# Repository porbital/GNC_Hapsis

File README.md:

# GNC_Hapsis

Software and hardware for GNC Hapsis.

    If you have any questions, please reach out to Matthew Allen on Slack.

## STAG Software 

The C++ code is stored in `STAG/flight_controller_v3`.

This was developed using PlatformIO, but can be used with Arduino IDE as well.

The current software is complete and will be used on the STAG mission. 

Hardware-in-the-loop is possible with this code setup, and can be enabled by commenting out the flag in `config.h`

## STAG PCB

The PCB for this project (version 4.1) is stored under `polaris4.1/`.

The current PCB is fully complete. I assembled it without a stencil, using solder paste and a hot plate. (In the future, it is worth buying a stencil).

### AI Transparency Statement

As I'm sure you all are aware, AI is an incredibly powerful tool. However, I think that it is important to be honest and clear regarding how it is utilized in a project, especially one of this nature.

AI was used for debugging, research, and some code generation (primarily autocomplete and boilerplate code). It also generated the flight visualization script.

# Go Orbital!

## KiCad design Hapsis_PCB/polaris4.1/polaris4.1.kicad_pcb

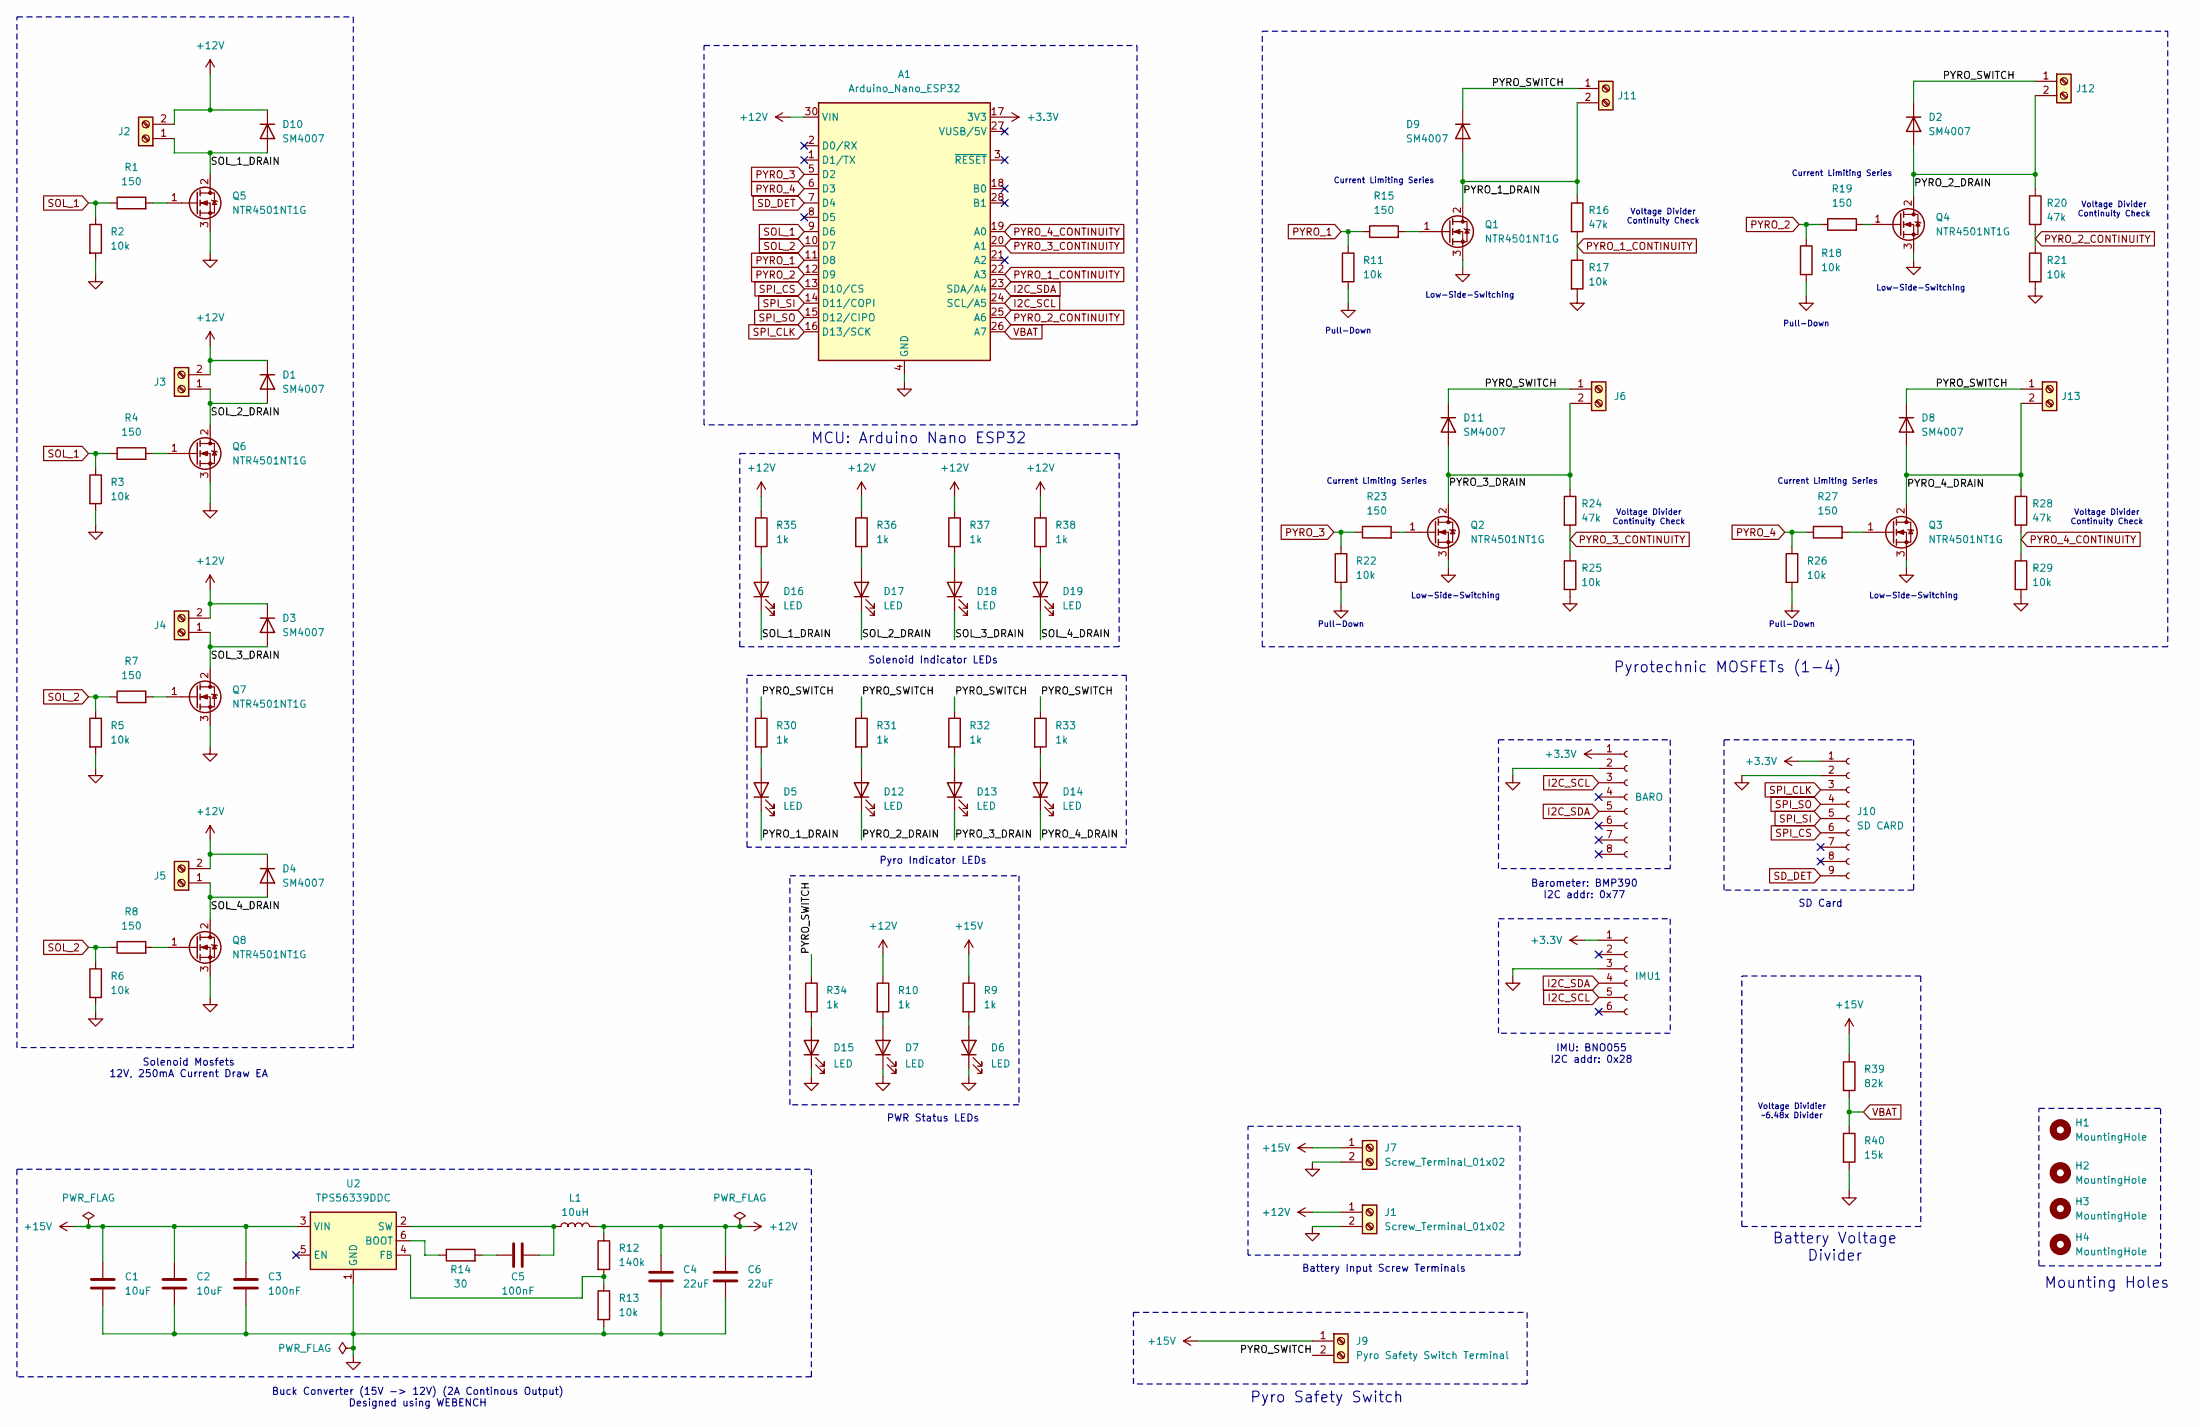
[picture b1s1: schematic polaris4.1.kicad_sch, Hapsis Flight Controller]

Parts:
A1: Arduino_Nano_ESP32; Arduino_Nano
C1, C2: 10uF; C_0805_2012Metric
C3, C5: 100nF; C_0805_2012Metric
C4, C6: 22uF; C_0805_2012Metric
D1, D2, D3, D4, D8, D9, D10, D11: SM4007; D_MELF
D5, D6, D7, D12, D13, D14, D15, D16, D17, D18, D19: LED; LED_0603_1608Metric
H1, H2, H3, H4: MountingHole; MountingHole_3mm
IMU1: Conn_01x06_Socket; PinHeader_1x06_P2.54mm_Vertical
J1, J7: Screw_Terminal_01x02; TerminalBlock_Phoenix_MKDS-1,5-2_1x02_P5.00mm_Horizontal
J2, J3, J4, J5, J6, J11, J12, J13: Screw_Terminal_01x02; TerminalBlock_RND_205-00276_1x02_P5.00mm_Vertical
J8: BARO; PinHeader_1x08_P2.54mm_Vertical
J9: Pyro Safety Switch Terminal; TerminalBlock_Phoenix_MKDS-1,5-2_1x02_P5.00mm_Horizontal
J10: SD CARD; PinHeader_1x09_P2.54mm_Vertical
L1: 10uH; L_Bourns_SRP1038C_10.0x10.0mm
Q1, Q2, Q3, Q4, Q5, Q6, Q7, Q8: NTR4501NT1G; SOT-23-3
R1, R4, R7, R8, R15, R19, R23, R27: 150; R_0805_2012Metric
R2, R3, R5, R6, R11, R17, R18, R21, R22, R25, R26, R29: 10k; R_0805_2012Metric
R9, R10, R30, R31, R32, R33, R34, R35, R36, R37, R38: 1k; R_0805_2012Metric
R12: 140k; R_0603_1608Metric
R13: 10k; R_0603_1608Metric
R14: 30; R_0603_1608Metric
R16, R20, R24, R28: 47k; R_0805_2012Metric
R39: 82k; R_0805_2012Metric
R40: 15k; R_0805_2012Metric
U2: TPS56339DDC; SOT-23-6

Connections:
+3.3V: A1.17 (3V3), IMU1.1, J8.1, J10.1
+12V: A1.30 (VIN), C4.1, C6.1, D1.1 (K), D3.1 (K), D4.1 (K), D10.1 (K), J1.1, J2.2, J3.2, J4.2, J5.2, L1.2, R10.1, R12.1, R35.1, R36.1, R37.1, R38.1
+15V: C1.1, C2.1, C3.1, J7.1, J9.1, R9.1, R39.1, U2.3 (VIN)
/PYRO_1_DRAIN: D5.1 (K), D9.2 (A), J11.2, Q1.2 (D), R16.1
/PYRO_2_DRAIN: D2.2 (A), D12.1 (K), J12.2, Q4.2 (D), R20.1
/PYRO_3_DRAIN: D11.2 (A), D13.1 (K), J6.2, Q2.2 (D), R24.1
/PYRO_4_DRAIN: D8.2 (A), D14.1 (K), J13.2, Q3.2 (D), R28.1
/PYRO_SWITCH: D2.1 (K), D8.1 (K), D9.1 (K), D11.1 (K), J6.1, J9.2, J11.1, J12.1, J13.1, R30.1, R31.1, R32.1, R33.1, R34.1
/SOL_1_DRAIN: D10.2 (A), D16.1 (K), J2.1, Q5.2 (D)
/SOL_2_DRAIN: D1.2 (A), D17.1 (K), J3.1, Q6.2 (D)
/SOL_3_DRAIN: D3.2 (A), D18.1 (K), J4.1, Q7.2 (D)
/SOL_4_DRAIN: D4.2 (A), D19.1 (K), J5.1, Q8.2 (D)
GND: A1.4 (GND), A1.29 (GND), C1.2, C2.2, C3.2, C4.2, C6.2, D6.1 (K), D7.1 (K), D15.1 (K), IMU1.3, J1.2, J7.2, J8.2, J10.2, Q1.3 (S), Q2.3 (S), Q3.3 (S), Q4.3 (S), Q5.3 (S), Q6.3 (S), Q7.3 (S), Q8.3 (S), R2.2, R3.2, R5.2, R6.2, R11.2, R13.2, R17.2, R18.2, R21.2, R22.2, R25.2, R26.2, R29.2, R40.2, U2.1 (GND)
I2C_SCL: A1.24 (SCL/A5), IMU1.5, J8.3
I2C_SDA: A1.23 (SDA/A4), IMU1.4, J8.5
unnamed: C5.2, R14.2
unnamed: D5.2 (A), R30.2
unnamed: D6.2 (A), R9.2
unnamed: D7.2 (A), R10.2
unnamed: D12.2 (A), R31.2
unnamed: D13.2 (A), R32.2
unnamed: D14.2 (A), R33.2
unnamed: D15.2 (A), R34.2
unnamed: D16.2 (A), R35.2
unnamed: D17.2 (A), R36.2
unnamed: D18.2 (A), R37.2
unnamed: D19.2 (A), R38.2
unnamed: Q1.1 (G), R15.2
unnamed: Q2.1 (G), R23.2
unnamed: Q3.1 (G), R27.2
unnamed: Q4.1 (G), R19.2
unnamed: Q5.1 (G), R1.2
unnamed: Q6.1 (G), R4.2
unnamed: Q7.1 (G), R7.2
unnamed: Q8.1 (G), R8.2
unnamed: R14.1, U2.6 (BOOT)
unnamed: R12.2, R13.1, U2.4 (FB)
unnamed: C5.1, L1.1, U2.2 (SW)
PYRO_1: A1.11 (D8), R11.1, R15.1
PYRO_1_CONTINUITY: A1.22 (A3), R16.2, R17.1
PYRO_2: A1.12 (D9), R18.1, R19.1
PYRO_2_CONTINUITY: A1.25 (A6), R20.2, R21.1
PYRO_3: A1.5 (D2), R22.1, R23.1
PYRO_3_CONTINUITY: A1.20 (A1), R24.2, R25.1
PYRO_4: A1.6 (D3), R26.1, R27.1
PYRO_4_CONTINUITY: A1.19 (A0), R28.2, R29.1
SD_DET: A1.7 (D4), J10.9
SOL_1: A1.9 (D6), R1.1, R2.1, R3.1, R4.1
SOL_2: A1.10 (D7), R5.1, R6.1, R7.1, R8.1
SPI_CLK: A1.16 (D13/SCK), J10.3
SPI_CS: A1.13 (D10/CS), J10.6
SPI_SI: A1.14 (D11/COPI), J10.5
SPI_SO: A1.15 (D12/CIPO), J10.4
VBAT: A1.26 (A7), R39.2, R40.1

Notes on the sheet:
Pyro Safety Switch
Low-Side-Switching
Voltage Divider Continuity Check
Barometer: BMP390 I2C addr: 0x77
Current Limiting Series
Solenoid Indicator LEDs
SD Card
Battery Voltage Divider
Pull-Down
Pyrotechnic MOSFETs (1-4)
Battery Input Screw Terminals
Buck Converter (15V -> 12V) (2A Continous Output) Designed using WEBENCH
Mounting Holes
MCU: Arduino Nano ESP32
IMU: BNO055 I2C addr: 0x28
Voltage Dividier ~6.48x Divider
PWR Status LEDs
Solenoid Mosfets 12V, 250mA Current Draw EA
Pyro Indicator LEDs

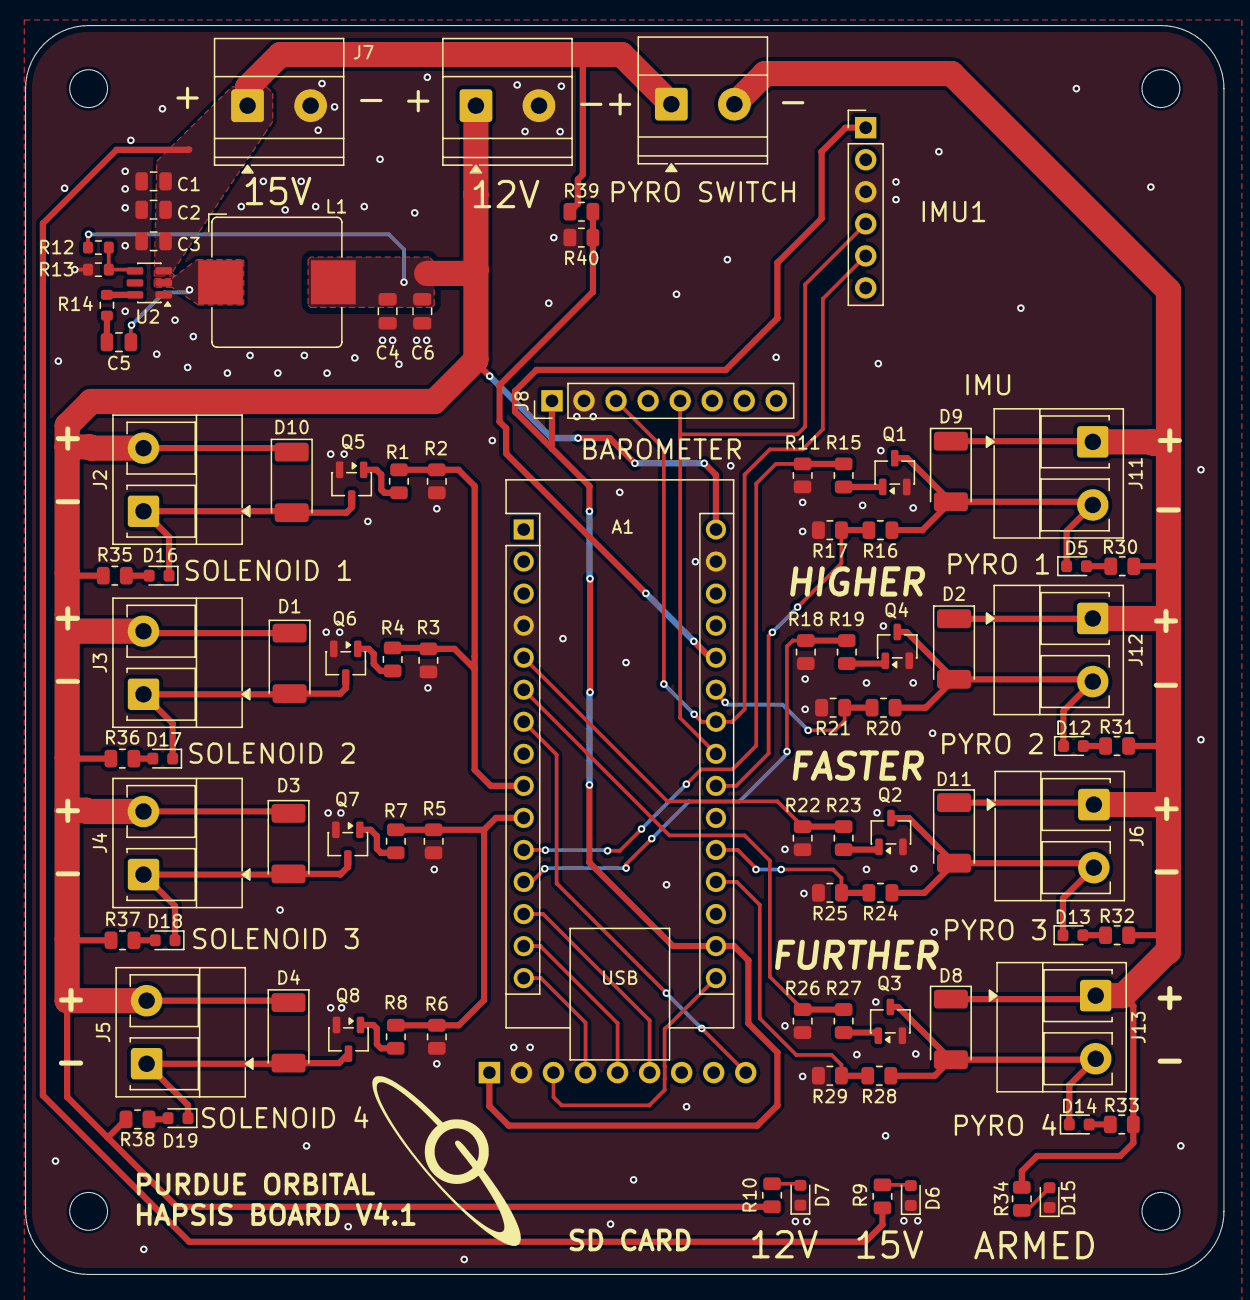
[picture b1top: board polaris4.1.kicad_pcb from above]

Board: 2 copper layers, 95.0 x 99.0 mm, 94 parts (1 on the bottom side), 54 nets.

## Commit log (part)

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2025-09-30 transfered GNC Polaris files to this github
2025-10-02 feature: Import legacy PurdueOrbital_GNC spring 25 work repo in Shashank's GIT into GNC_theory_spring25
2025-10-02 Adding mattallen archives
    Mat Allen archives were missing
2025-10-15 added readme
2025-10-15 updated documention
2025-10-30 10-30-25 test. added files
2025-11-04 Pulled data from Sd card 11/3
2025-11-04 Bunch o random stuff
2025-11-04 Put all data in here
2025-11-06 changing the file format for new test log
2025-11-06 Squashed commit of the following:
    commit 1dba94bd67e0e9e9782bb02605f0dda92fad6f34
    Author: Shashank Aritottam Namboodiri <snambood@purdue.edu>
    Date: Wed Nov 5 19:39:24 2025 -0500
    changing the file format for new test log
    commit 669e1e16f98d1be8ff5be52fef48e35af7ce78f7
    Author: Shashank Aritottam Namboodiri <snambood@purdue.edu>
2025-11-06 Found the files to analyse
    006 124 224 524 837
2025-11-11 Made a square wave test algorithm
2025-11-13 added tests from 11-12
2025-11-13 added test scripts and files
2026-02-16 added PCB
2026-02-19 added STAG code
2026-02-19 updated README for documentation
2026-03-04 added newest version (4.1) of pcb
2026-03-04 updated PCB
2026-03-13 flight controller firmware v2
2026-04-20 updated final code and pcd files for STAG mission
